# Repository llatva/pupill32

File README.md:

# pu(rple)pill32
## Compact and inexpensive USB-C development board for PY32F030 (TSSOP20) 32-bit MCU

RevA had some glitches, please refer to changelog in the revB schematic or below.
RevB tested to be functional, and can be flash-programmed over USB (see bootloader access below).

## Features

* development/evaluation board for Pyua PY32F030F1xP6 MCU (TSSOP20)
* USB serial (CH340N, ESD protection)
* USB bootloader support (e.g. puyaisp.py from MCU-Flash-Tools /1/)
* 48 MHz operation with internal oscillator
* option for 32.768 kHz crystal (if used, pins PA9 and PA10 reserved)
* all peripheral pins available
* SWD header for programming (by using USB bootloader for flashing, those pins can be configured for other purposes**)
* 3V3 linear regulator; 3V3 logic levels
* powered from USB (SMD fuse for overcurrent protection)
* PWR LED and user-programmable USR led (activated by solder bridge)
* RESET and BOOT buttons

**) In that case, if you don't need pull-ups for your signals, do not populate R11-R12.

## Bootloader access

USB UART is connected to PA2/PA3 (TX/RX). To access bootloader (e.g. puyaisp.py /1/, USB-to-serial), either

* Disconnect USB cable, press and hold BOOT button then connect the cable.

OR 

* Connect USB cable, press and hold BOOT button and press and release RESET button

/1/ [https://github.com/wagiminator/MCU-Flash-Tools]

## Images

## Changelog revA --> revB

* added C19 (bug)
* swapped UART RX/TX (bug)
* added R1 (boot0 pulldown)
* R2 -> 5k1 (brightness)
* C20 tantalum
* SWD resistors R9-R12 added

## Independent project -- no affiliation or endorsement

This project is no way affiliated with Puya Semiconductor or any other commercial body. This is an indie evaluation board designed and built by a hobbyist. You may use this open hardware design, at your own risk, according to its license conditions, see the following chapter. 

## References

/2/ [J. Carlson: The cheapest flash microcontroller you can buy is actually an ARM CORTEX-M0+](https://jaycarlson.net/2023/02/04/the-cheapest-flash-microcontroller-you-can-buy-is-actually-an-arm-cortex-m0/)

/3/ [OpenPuya -- py32.org](https://py32.org/en/)

## License

This board is licensed under CERN Open Hardware License, version 2, CERN-OHL-W (weakly reciprocal). 

Please refer to LICENSE file for more information.

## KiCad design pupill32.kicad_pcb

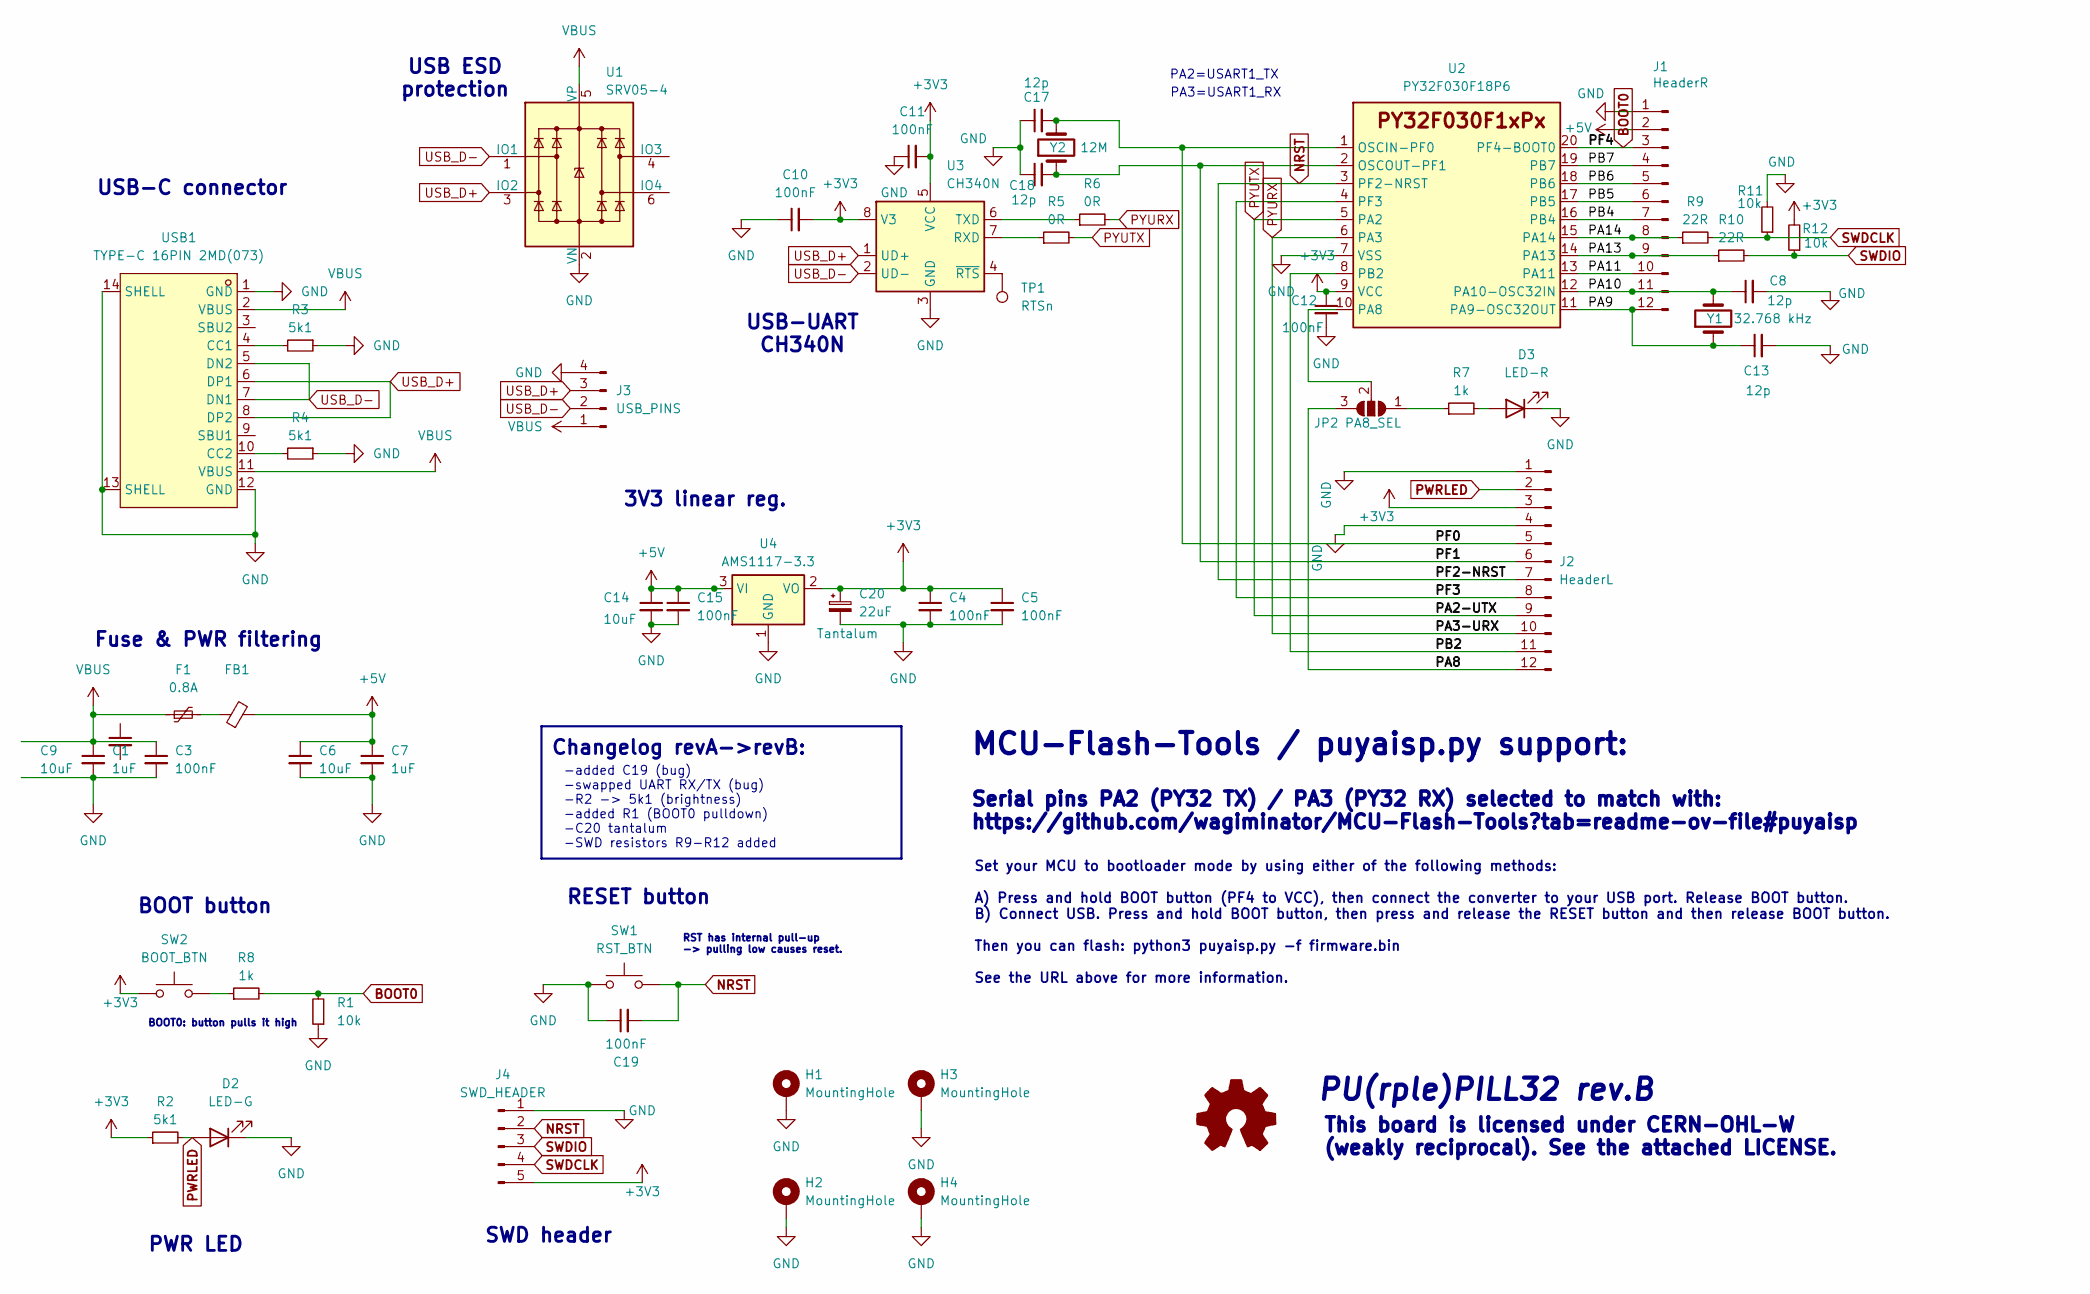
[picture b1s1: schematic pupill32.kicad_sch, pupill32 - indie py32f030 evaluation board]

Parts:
C1, C7: 1uF; C_0805_2012Metric_Pad1.18x1.45mm_HandSolder
C3, C4, C5, C10, C11, C12, C15, C19: 100nF; C_0805_2012Metric_Pad1.18x1.45mm_HandSolder
C6, C9, C14: 10uF; C_0805_2012Metric_Pad1.18x1.45mm_HandSolder
C8, C13, C17, C18: 12p; C_0805_2012Metric_Pad1.18x1.45mm_HandSolder
C20: 22uF; CP_EIA-3528-21_Kemet-B_Pad1.50x2.35mm_HandSolder
D2: LED-G; LED_0805_2012Metric_Pad1.15x1.40mm_HandSolder
D3: LED-R; LED_0805_2012Metric_Pad1.15x1.40mm_HandSolder
F1: 0.8A; Fuse_1206_3216Metric_Pad1.42x1.75mm_HandSolder
FB1: L_1206_3216Metric_Pad1.42x1.75mm_HandSolder
H1, H2, H3, H4: MountingHole; MountingHole_2.7mm_M2.5_ISO7380_Pad
J1: HeaderR; PinHeader_1x12_P2.54mm_Vertical
J2: HeaderL; PinHeader_1x12_P2.54mm_Vertical
J3: USB_PINS; PinHeader_1x04_P2.00mm_Vertical
J4: SWD_HEADER; PinHeader_1x05_P2.54mm_Vertical
JP2: PA8_SEL; SolderJumper-3_P1.3mm_Open_RoundedPad1.0x1.5mm
R1, R11, R12: 10k; R_0805_2012Metric_Pad1.20x1.40mm_HandSolder
R2, R3, R4: 5k1; R_0805_2012Metric_Pad1.20x1.40mm_HandSolder
R5, R6: 0R; R_0805_2012Metric_Pad1.20x1.40mm_HandSolder
R7, R8: 1k; R_0805_2012Metric_Pad1.20x1.40mm_HandSolder
R9, R10: 22R; R_0805_2012Metric_Pad1.20x1.40mm_HandSolder
SW1: RST_BTN; SW-SMD_L6.0-W3.5-LS8.2
SW2: BOOT_BTN; SW-SMD_L6.0-W3.5-LS8.2
TP1: RTSn; TestPoint_Pad_D1.0mm
U1: SRV05-4; SOT-23-6
U2: PY32F030F18P6; TSSOP-20_4.4x6.5mm_P0.65mm
U3: CH340N; SOP-8_3.9x4.9mm_P1.27mm
U4: AMS1117-3.3; SOT-223-3_TabPin2
USB1: TYPE-C 16PIN 2MD(073); USB-C-SMD_TYPE-C-6PIN-2MD-073; LCSC Part C2765186
Y1: 32.768 kHz; Crystal_Round_D2.0mm_Vertical
Y2: 12M; Crystal_HC49-4H_Vertical

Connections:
+3V3: C4.1, C5.1, C10.2, C11.2, C12.1, C20.1, J2.3, J4.5, R2.1, R12.2, SW2.1, U2.9 (VCC), U3.5 (VCC), U3.8 (V3), U4.2 (VO)
+5V: C6.1, C7.1, C14.1, C15.1, FB1.2, J1.2, U4.3 (VI)
/PA8: J2.12, JP2.3 (B)
/PA9: C13.1, J1.12, U2.11 (PA9-OSC32OUT), Y1.1
/PA10: C8.1, J1.11, U2.12 (PA10-OSC32IN), Y1.2
/PA11: J1.10, U2.13 (PA11)
/PA13: J1.9, R10.1, U2.14 (PA13)
/PA14: J1.8, R9.1, U2.15 (PA14)
/PB2: J2.11, U2.8 (PB2)
/PB4: J1.7, U2.16 (PB4)
/PB5: J1.6, U2.17 (PB5)
/PB6: J1.5, U2.18 (PB6)
/PB7: J1.4, U2.19 (PB7)
/PF0: C17.2, J2.5, U2.1 (OSCIN-PF0), Y2.2
/PF1: C18.2, J2.6, U2.2 (OSCOUT-PF1), Y2.1
/PF3: J2.8, U2.4 (PF3)
BOOT0: J1.3, R1.2, R8.2, U2.20 (PF4-BOOT0)
GND: C1.2, C3.2, C4.2, C5.2, C6.2, C7.2, C8.2, C10.1, C11.1, C12.2, C13.2, C14.2, C15.2, C17.1, C18.1, C19.1, C20.2, D2.1 (K), D3.1 (K), H1.1, H2.1, H3.1, H4.1, J1.1, J2.1, J2.4, J3.4, J4.1, R1.1, R3.1, R4.1, R11.2, SW1.1, U1.2 (VN), U2.7 (VSS), U3.3 (GND), U4.1 (GND), USB1.1 (GND), USB1.12 (GND), USB1.13 (SHELL), USB1.14 (SHELL)
NRST: C19.2, J2.7, J4.2, SW1.2, U2.3 (PF2-NRST)
unnamed: D3.2 (A), R7.2
unnamed: F1.2, FB1.1
unnamed: JP2.1 (A), R7.1
unnamed: JP2.2 (C), U2.10 (PA8)
unnamed: R8.1, SW2.2
unnamed: R5.1, U3.7 (RXD)
unnamed: R6.1, U3.6 (TXD)
unnamed: TP1.1, U3.4 (~RTS)
unnamed: R3.2, USB1.4 (CC1)
unnamed: R4.2, USB1.10 (CC2)
PWRLED: D2.2 (A), J2.2, R2.2
PYURX: J2.10, R6.2, U2.6 (PA3)
PYUTX: J2.9, R5.2, U2.5 (PA2)
SWDCLK: J4.4, R9.2, R11.1
SWDIO: J4.3, R10.2, R12.1
USB_D+: J3.3, U1.3 (IO2), U3.1 (UD+), USB1.6 (DP1), USB1.8 (DP2)
USB_D-: J3.2, U1.1 (IO1), U3.2 (UD-), USB1.5 (DN2), USB1.7 (DN1)
VBUS: C1.1, C3.1, F1.1, J3.1, U1.5 (VP), USB1.2 (VBUS), USB1.11 (VBUS)

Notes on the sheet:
-added C19 (bug) -swapped UART RX/TX (bug) -R2 -> 5k1 (brightness) -added R1 (BOOT0 pulldown) -C20 tantalum -SWD resistors R9-R12 added
RESET button
This board is licensed under CERN-OHL-W (weakly reciprocal). See the attached LICENSE.
Serial pins PA2 (PY32 TX) / PA3 (PY32 RX) selected to match with: https://github.com/wagiminator/MCU-Flash-Tools?tab=readme-ov-file#puyaisp
PA3=USART1_RX
3V3 linear reg.
Fuse & PWR filtering
MCU-Flash-Tools / puyaisp.py support:
USB-C connector
PWR LED
USB ESD protection
PA2=USART1_TX
RST has internal pull-up -> pulling low causes reset.
Changelog revA->revB:
BOOT button
USB-UART CH340N
BOOT0: button pulls it high
PU(rple)PILL32 rev.B
Set your MCU to bootloader mode by using either of the following methods: A) Press and hold BOOT button (PF4 to VCC), then connect the converter to your USB port. Release BOOT button. B) Connect USB. Press and hold BOOT button, then press and release the RESET button and then release BOOT button. T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
SWD header

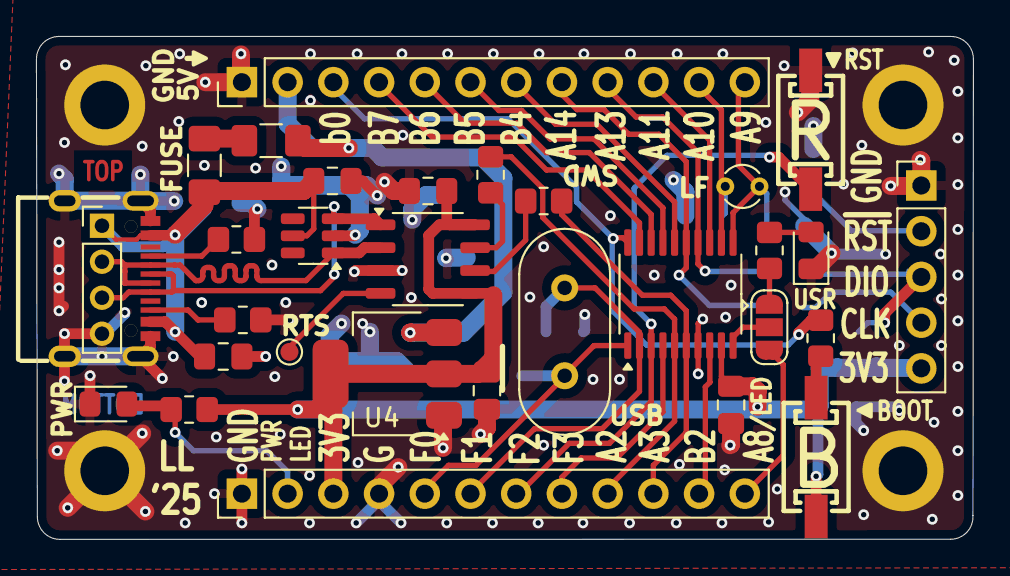
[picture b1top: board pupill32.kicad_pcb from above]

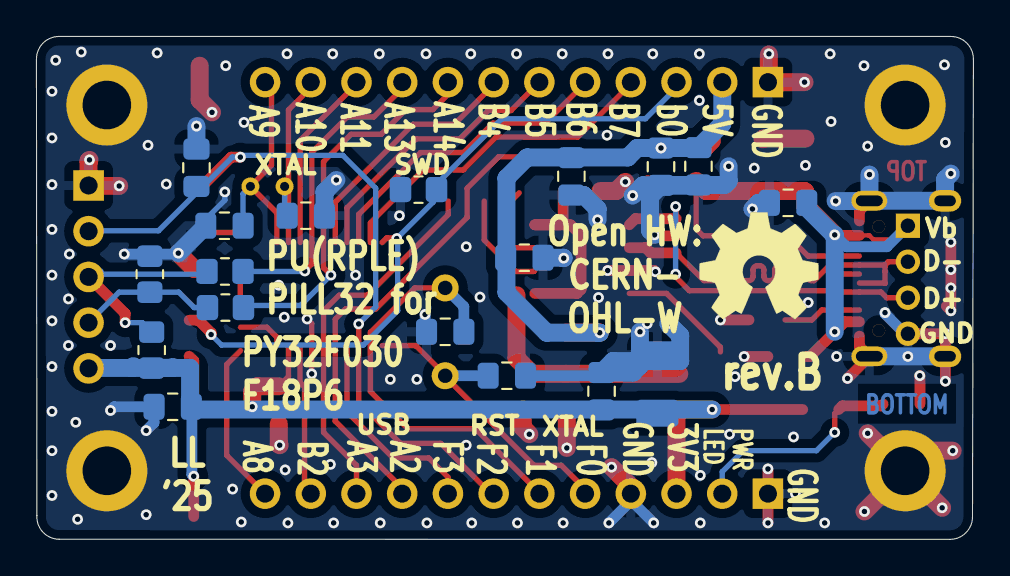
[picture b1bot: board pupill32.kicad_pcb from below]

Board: 2 copper layers, 52.1 x 27.9 mm, 54 parts (19 on the bottom side), 37 nets.

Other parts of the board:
OHW: OSHW-Symbol_6.7x6mm_SilkScreen

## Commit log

2024-07-22 first commit to repo
2024-07-22 intermediate save
2024-07-22 switch footprint and 3d
2024-07-22 readme update
2024-07-22 some progress
2024-07-22 to be continued
2024-07-23 silks and some routing, to be continued
2024-07-23 further
2024-07-23 almost ready
2024-07-24 checking and verifying still
2024-07-24 some fine-tuning
2024-07-24 schema to pdf
2024-07-24 LICENSE
2024-07-24 note text edit
2024-07-24 update schema PDF
2024-07-24 fix uart pins
2024-07-24 added pad for RTS pin
2024-08-01 added HF crystal
2024-08-01 texts edit
2024-08-01 minor text position fix
2024-08-01 added GND via
2024-08-01 updated schema PDF
2024-12-14 3d workflow
2024-12-14 project rename
2024-12-14 project rename, part2
2024-12-14 rename schema (project rename)
2024-12-14 project rename, part3
2024-12-14 fix workflow (project name)
2024-12-14 typofix in readme
2024-12-14 deploy v
2024-12-14 upload to v4
2024-12-14 Revert "fix workflow (project name)"
    This reverts commit f6ac1b56378155b12190a51ced1e397e132e427e.
2024-12-14 revert version changes
2024-12-14 versions tuning still
2024-12-14 remove unnecessary images dir from repo
2024-12-14 try zoom 2
2024-12-14 try zoom 1.5
2024-12-14 added 3d images to README
2024-12-14 readme
2024-12-15 update schematic, rename file
2024-12-15 typofix
2024-12-15 reference to puyaisp.py
2025-01-03 revA errata -> revB
2025-01-03 readme markup fix
2025-01-03 note on revB
2025-01-03 update workflow to upload artifact v4
2025-01-03 Revert "update workflow to upload artifact v4"
    This reverts commit 946600c552cfdf21525bf0f0212f1c945cad86df.
2025-01-03 test actions/upload-pages-artifact@v3
2025-01-03 Revert "test actions/upload-pages-artifact@v3"
    This reverts commit 71d8e9a5d5ab0071f8765f5fd9443ac8c90af546.
2025-01-03 remove revA schema pdf
2025-01-03 add references
2025-01-03 added missing linefeed
2025-01-03 schema update (stylish changes, no content changes)
2025-01-04 R1 boot0 pulldown
2025-01-04 schema changelog update
2025-01-10 tantalum
2025-01-10 SWD resistors, changelog update
2025-01-10 minor tuning
2025-01-10 tantalum silk
2025-01-10 bot silks
2025-01-11 SWCLK pulled down (corrected)
2025-04-12 README update, photo of revB
